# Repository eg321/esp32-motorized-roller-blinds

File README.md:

Button control modified to use only one button per 1 blind

Short click - open

Long press - close

5 clicks - restart esp

Only Button UP pin used. 

Optional support light sensor BH1750 on GPIO 5 pin. 
Value can be obtained from MQTT topic ESP_blinds/chip_ID/out/lux

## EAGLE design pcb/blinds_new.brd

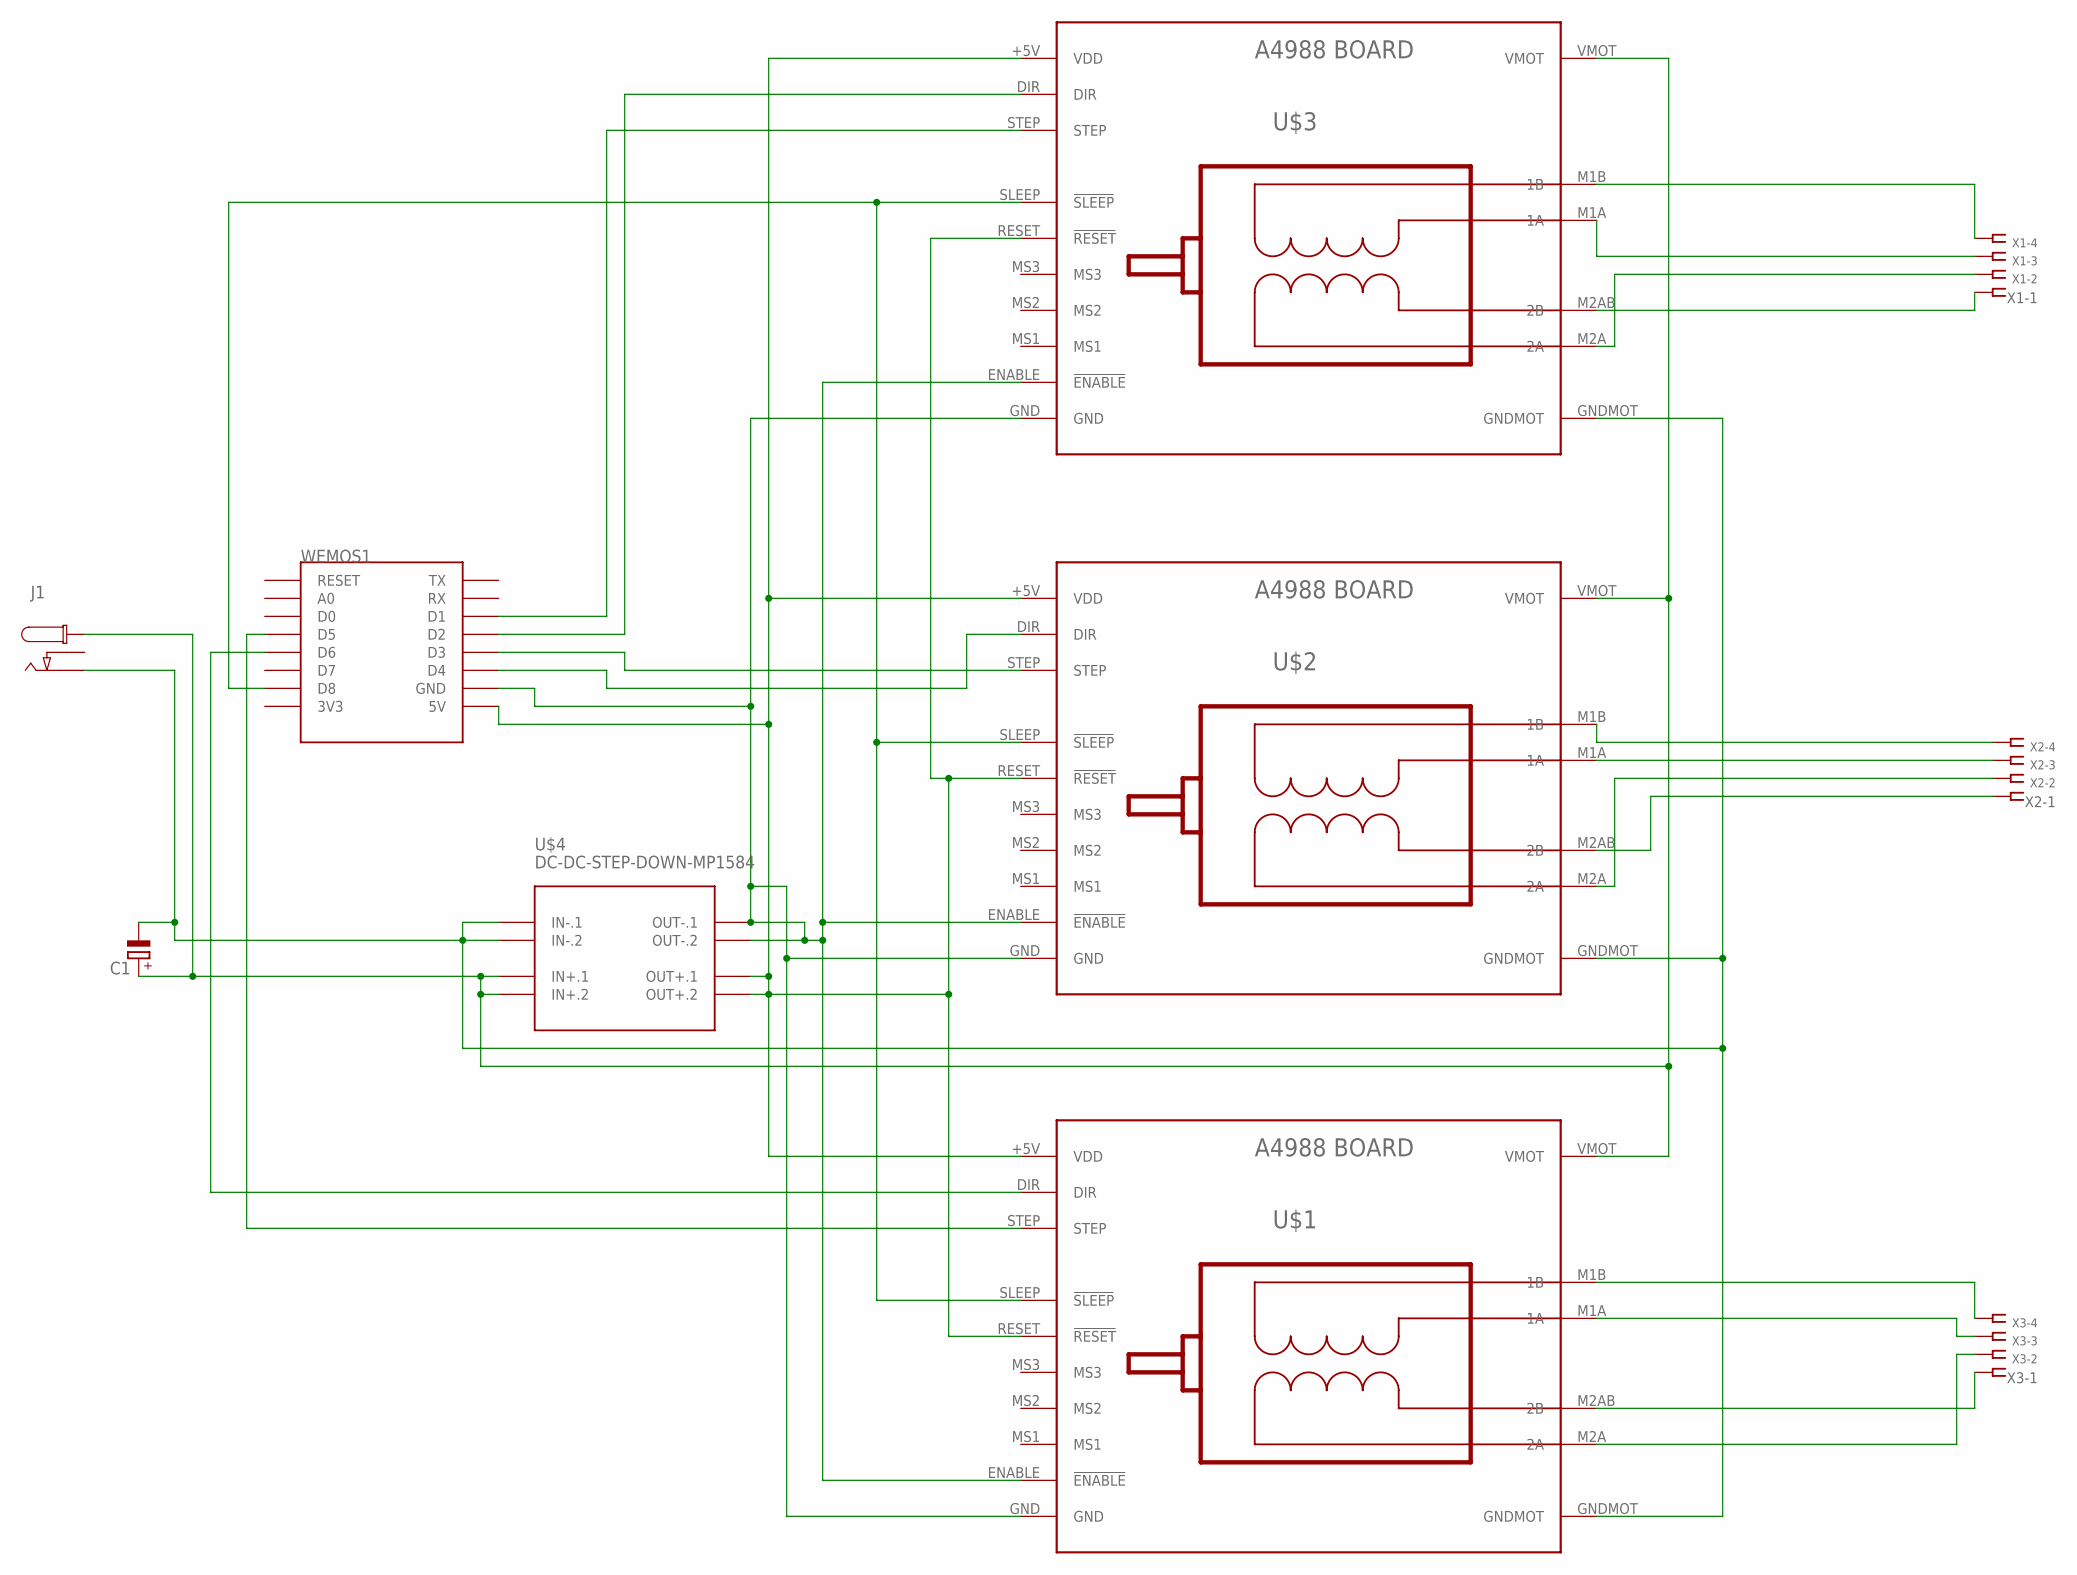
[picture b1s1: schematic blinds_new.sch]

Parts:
C1: CPOL-EUE1.8-4; E1,8-4
J1: CON_DC_M-DC_SMD; DC_BARREL_JACK_SMD_2MM
U$1, U$2, U$3: BOARD_A4988
U$4: DC-DC-STEP-DOWN-MP1584
WEMOS1: WEMOS-D1-MINI
X1, X2, X3: SSW-104-02-S-S

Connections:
unnamed: U$1.+5V (VDD), U$1.RESET (!RESET), U$2.+5V (VDD), U$2.RESET (!RESET), U$3.+5V (VDD), U$3.RESET (!RESET), U$4.OUT+.1, U$4.OUT+.2, WEMOS1.5V
unnamed: U$1.ENABLE (!ENABLE), U$1.GND, U$2.ENABLE (!ENABLE), U$2.GND, U$3.ENABLE (!ENABLE), U$3.GND, U$4.OUT-.1, U$4.OUT-.2, WEMOS1.GND
unnamed: U$3.M1B (1B), X1.4
unnamed: U$3.M1A (1A), X1.3
unnamed: U$1.M2A (2A), X3.2
unnamed: U$1.M2AB (2B), X3.1
unnamed: U$2.M1B (1B), X2.4
unnamed: U$2.M1A (1A), X2.3
unnamed: U$2.M2AB (2B), X2.1
unnamed: U$2.M2A (2A), X2.2
unnamed: U$1.M1B (1B), X3.4
unnamed: U$1.M1A (1A), X3.3
unnamed: U$3.M2AB (2B), X1.1
unnamed: U$3.M2A (2A), X1.2
unnamed: U$1.SLEEP (!SLEEP), U$2.SLEEP (!SLEEP), U$3.SLEEP (!SLEEP), WEMOS1.D8
unnamed: C1.-, J1.P2, U$1.GNDMOT, U$2.GNDMOT, U$3.GNDMOT, U$4.IN-.1, U$4.IN-.2
unnamed: U$3.STEP, WEMOS1.D1
unnamed: U$3.DIR, WEMOS1.D2
unnamed: U$2.STEP, WEMOS1.D3
unnamed: U$2.DIR, WEMOS1.D4
unnamed: U$1.STEP, WEMOS1.D5
unnamed: U$1.DIR, WEMOS1.D6
unnamed: C1.+, J1.P1@2 (P1), U$1.VMOT, U$2.VMOT, U$3.VMOT, U$4.IN+.1, U$4.IN+.2

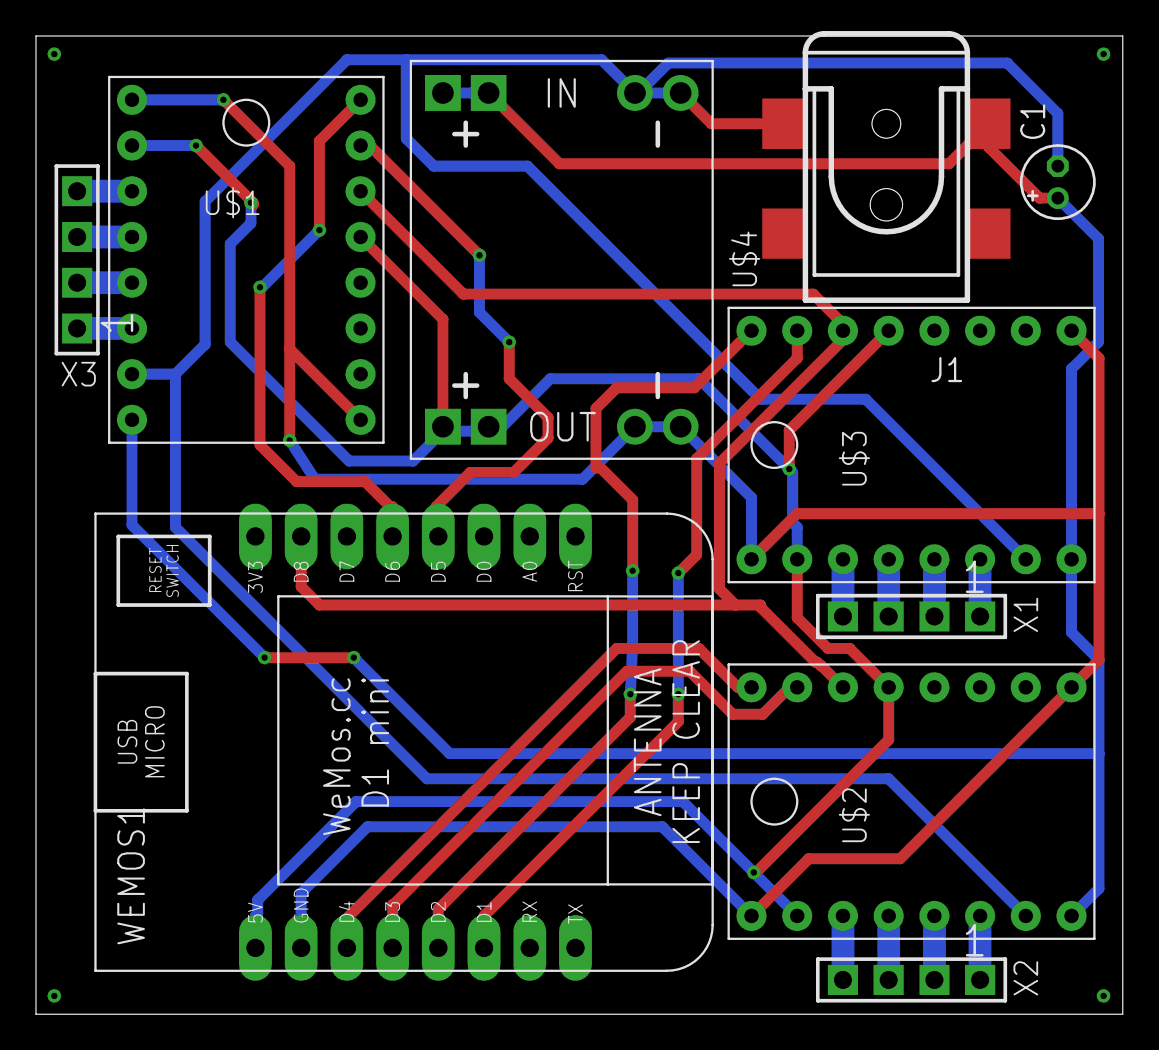
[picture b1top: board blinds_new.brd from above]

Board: 2 copper layers, 60.4 x 54.3 mm, 10 parts (0 on the bottom side), 23 nets.

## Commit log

2019-09-17 Project customization to 3 motors
    - project ported to Platformio
    - changed 3d parts according to small tube ~16mm
    - added functionality of 3 step motors
    - add current state broadcasting during blinds moving
    - add wipe setting function
    - add pcb sources
2020-01-09 Switched back to Stepper_28BYJ_48
2020-01-09 Updated 3d parts (Leroy Merlin version)
2020-01-09 This repo is not archieved more :)
2020-09-13 ESP32 support, moving to CheapStepper, error handling for MQTT connection
2020-09-15 Moving to ESP-WiFiSettings library
2021-03-13 Try to reconnect to the MQTT automatically (each 60 sec)
2021-03-13 Use esptool as default protocol AND update version to 1.4.1
2021-03-13 Fix update notifications and links
2021-04-28 Add support for Up / Down mechanical buttons
2021-07-05 Add missing dependencies
2021-07-05 Fix working with LittleFS on ESP8266
2021-07-05 Configure up/down buttons dynamically at portal
2021-07-08 TECH Automatically reformat code (4 spaces per tab + brackets)
2021-07-11 [v2.0] Dynamic configuration of steppers and pins at captive portal (huge refactoring)
2021-07-12 [v2.0] MQTT refactoring and other optimizations
2021-07-12 [v2.0] Buttons - another press to the same direction will cause stop of steppers
2021-07-12 [v2.0] "stop" is explicit command now + fixes with buttons
2021-07-27 Preparing 2.0 release (Russian version of README.md)
2021-08-01 [v2.0] cosmetic changes for Russian readme
2021-08-01 Insert images
2021-08-01 [v2.0] Update readme.md
2021-08-14 #1 Adding possibility to restart controller from mechanical buttons (5 clicks by default)
2021-10-28 #9 Don't try to connect with disabled MQTT
2021-11-07 #1 Check for WiFi connection and restart on failure timeout
2021-11-08 Implement Autodiscovery for HomeAssistant
2021-11-08 Implement Autodiscovery for HomeAssistant - add availability messages
2021-11-08 Make checking of intervals reliable (overflow issue)
2021-11-21 Autodiscovery message should be retained
2021-12-11 Resolve compilation issues for ESP8266 (abs -> fabs)
2021-12-11 Update readme (MQTT auto-discovery)
2021-12-11 Update readme (MQTT auto-discovery) #2
2021-12-11 Delete index_html.h
    delete unused file
2022-07-21 Update main.cpp
    Add lux sensor bh1750 support (off by default)
2022-11-29 new chip id generation
2024-09-22 Add ozon home blinds direct drive shaft

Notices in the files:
parts and their libraries:
diy-modules: Released under the Creative Commons Attribution 4.0 International License: http://creativecommons.org/licenses/by/4.0
